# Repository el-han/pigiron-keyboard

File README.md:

# Pigiron keyboard

The Pigiron keyboard is a 80 % ISO keyboard. It may be used on it's own or together with the nmblock of the [Ingot keyboard](https://github.com/el-han/ingot-keyboard).

## Features

- QMK firmware
- Cherry MX switches
- WS2812 RGB LEDs under each switch
- PCB plate for plate mounted switches

## Todo

- Add picture
- Merge firmware into QMK project

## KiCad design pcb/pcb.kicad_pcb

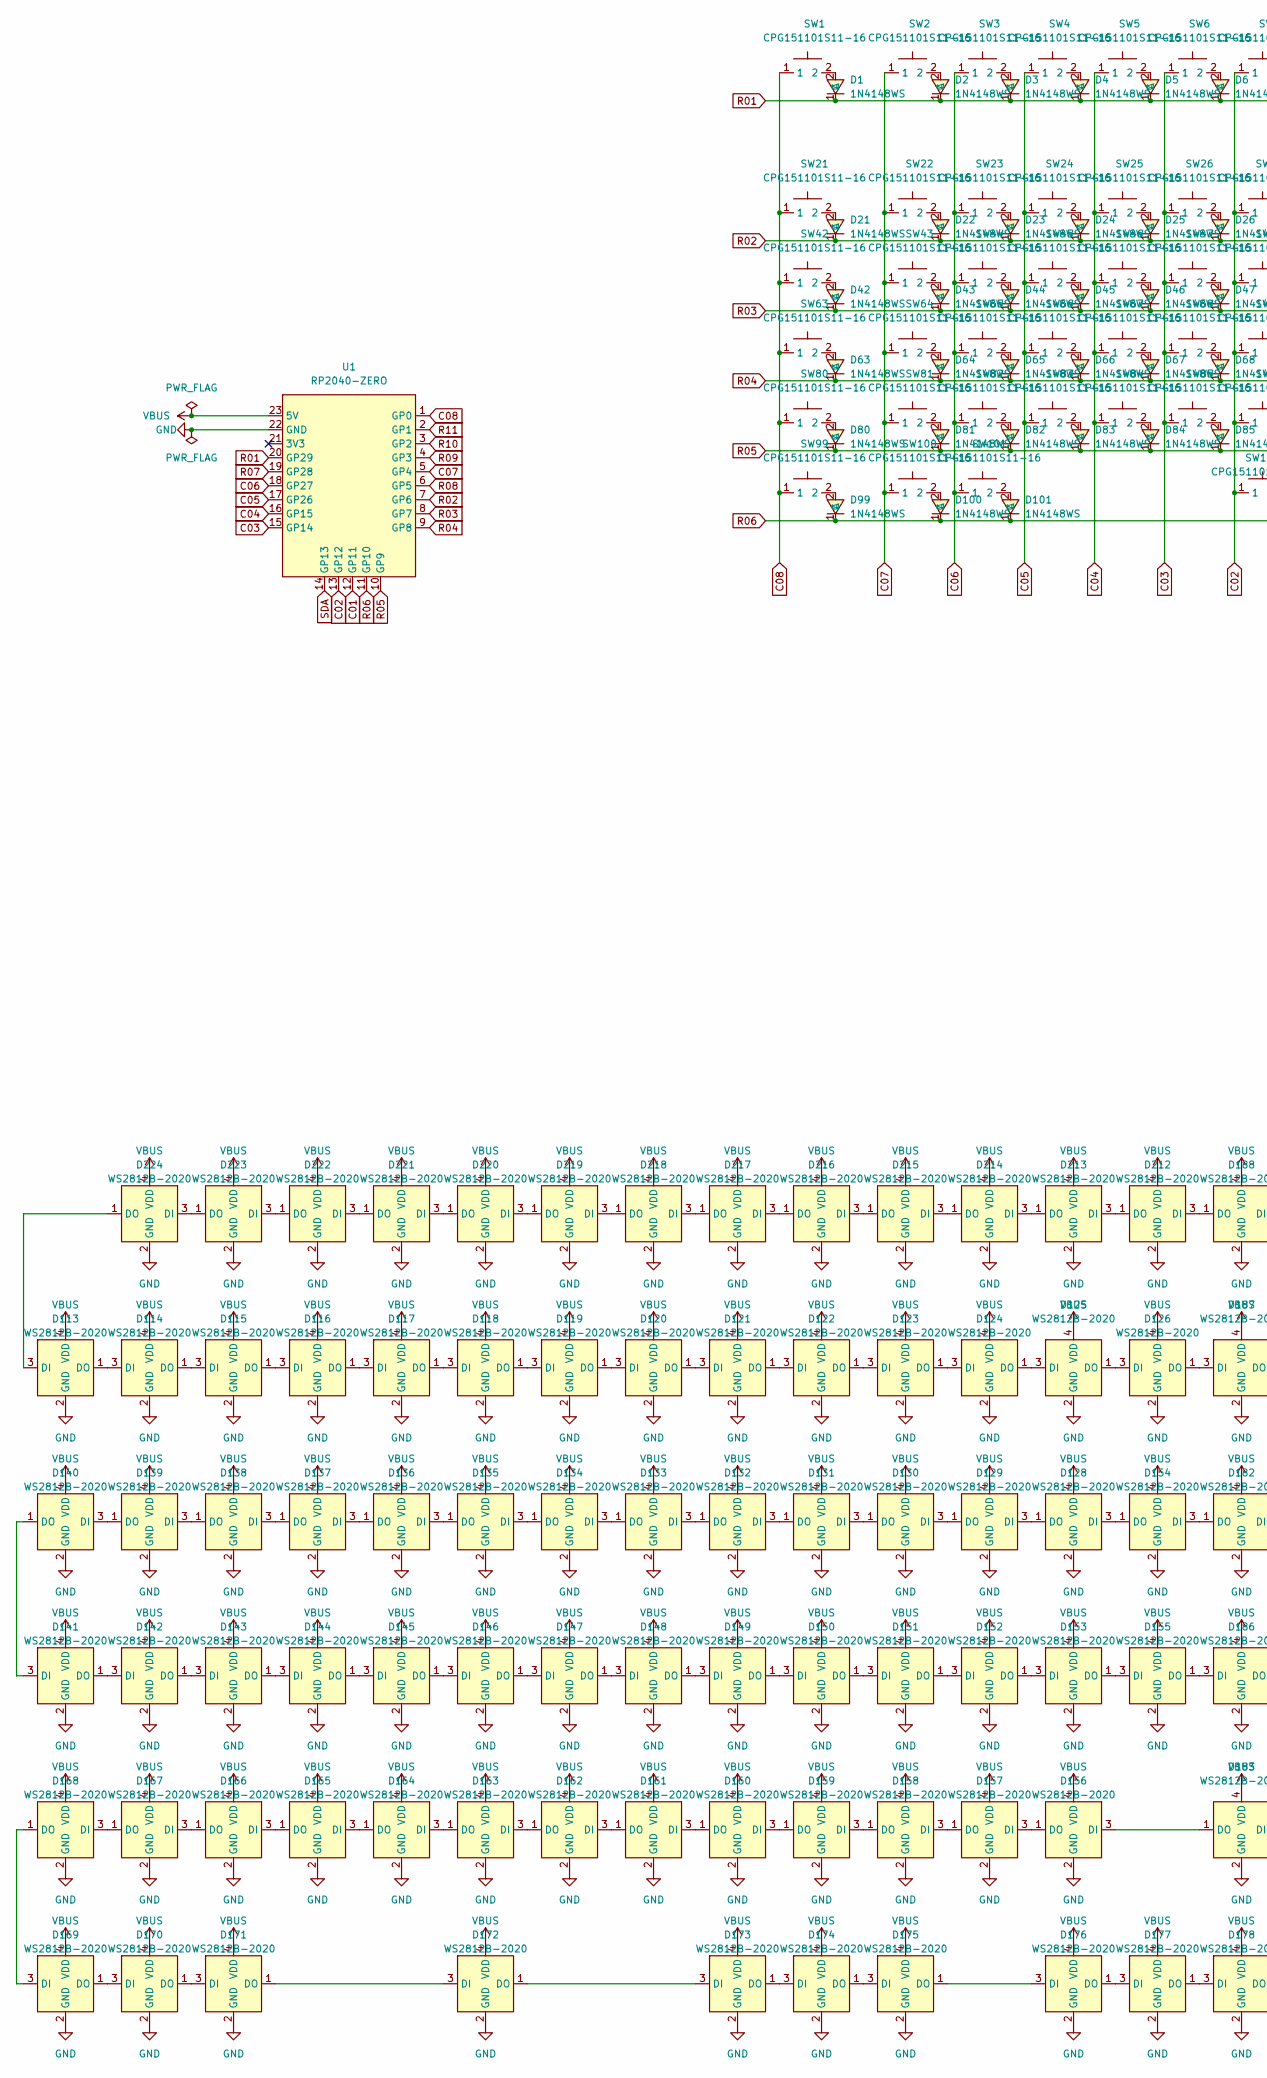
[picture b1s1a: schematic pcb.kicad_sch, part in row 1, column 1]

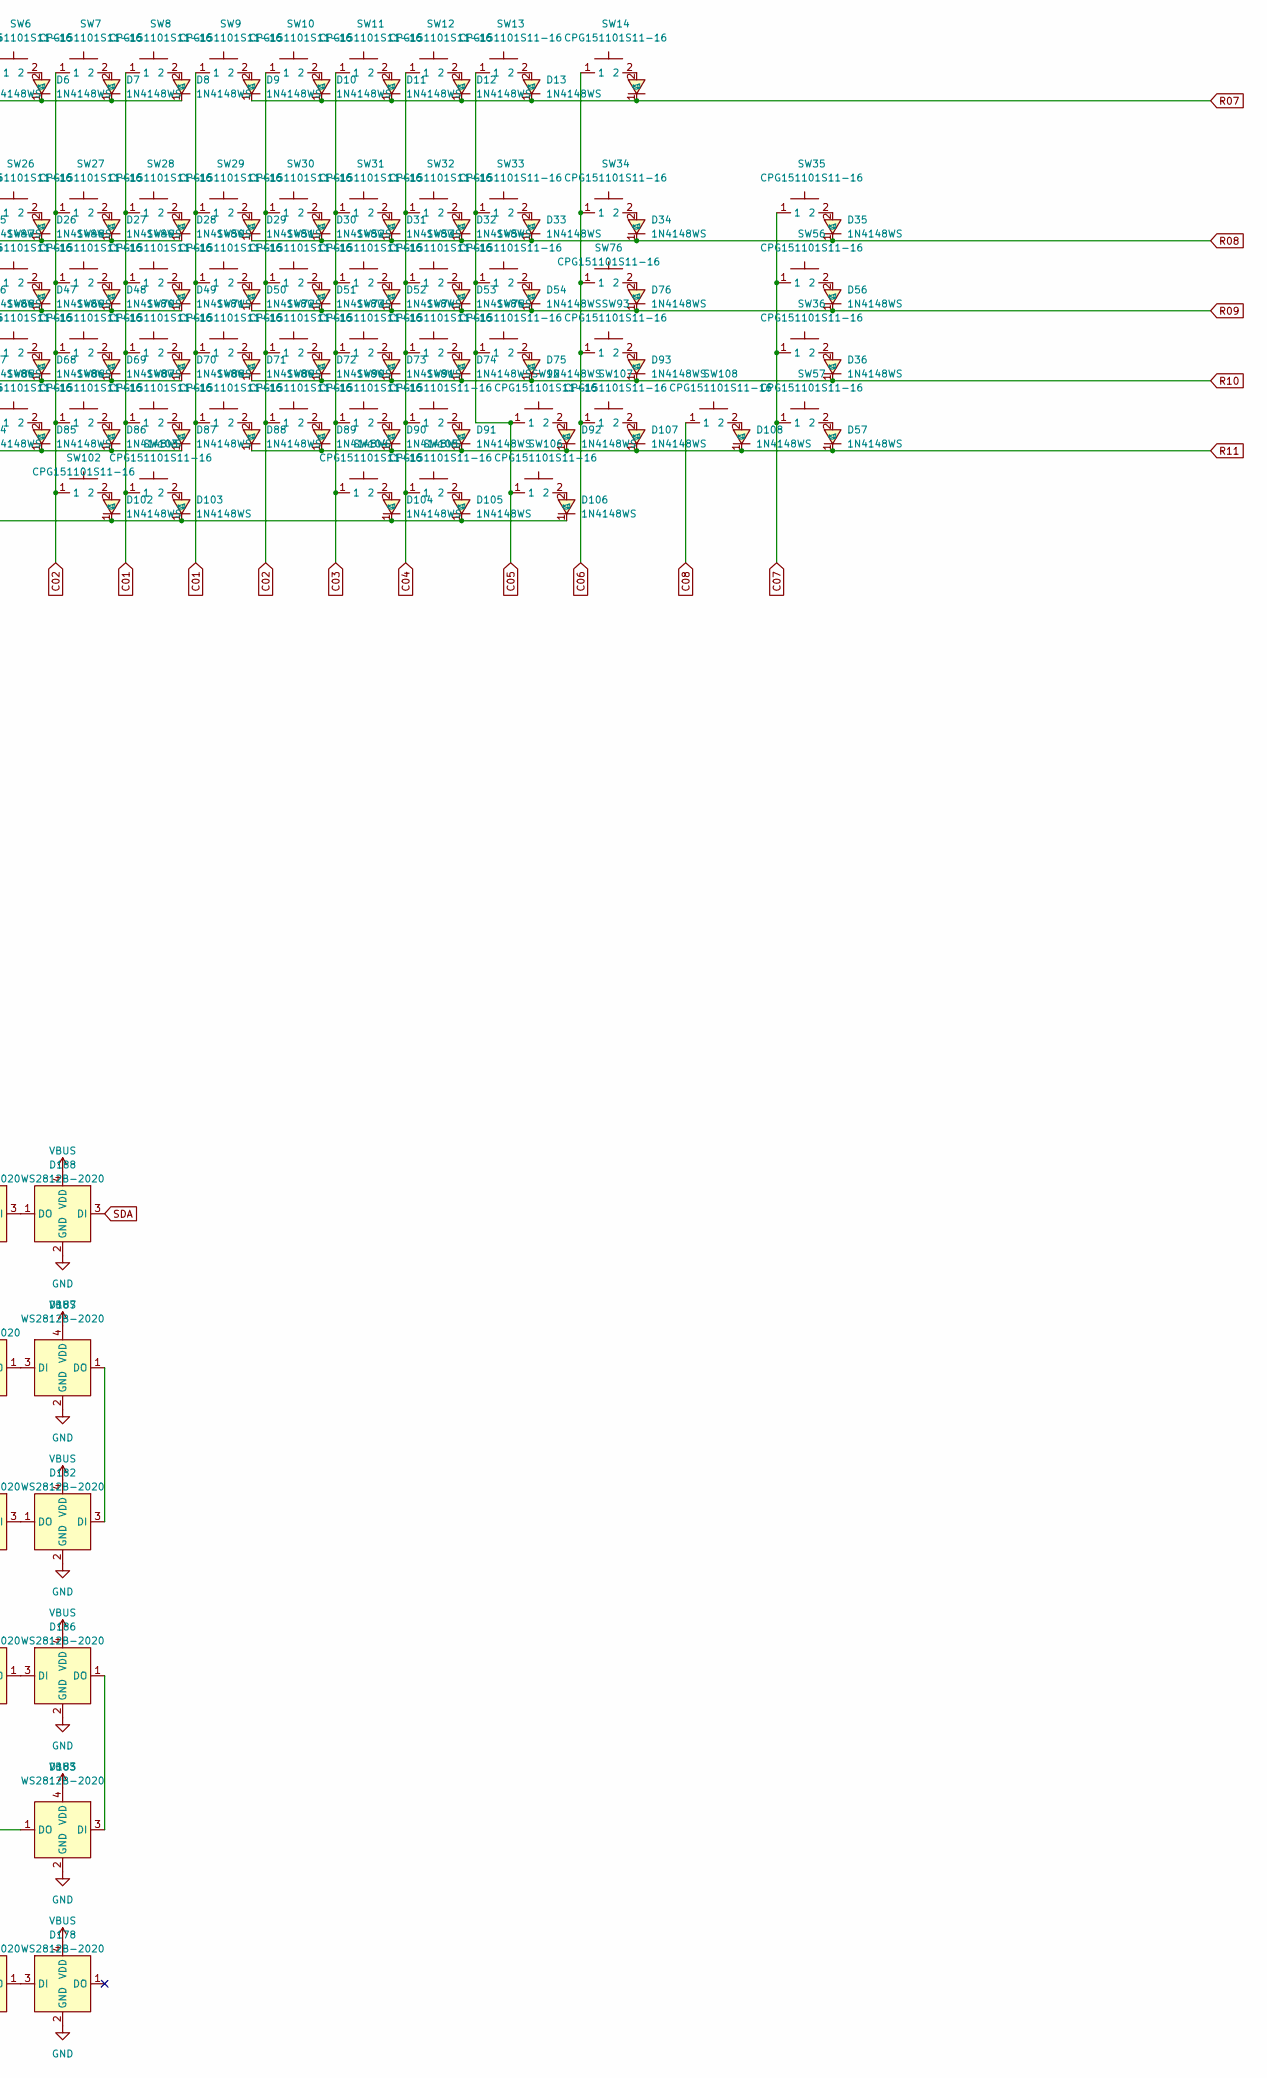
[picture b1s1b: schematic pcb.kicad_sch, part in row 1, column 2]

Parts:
D1, D2, D3, D4, D5, D6, D7, D8, D9, D10, D11, D12, D13, D14, D21, D22, D23, D24, D25, D26, D27, D28, D29, D30, D31, D32, D33, D34, D35, D36, D42, D43, D44, D45, D46, D47, D48, D49, D50, D51, D52, D53, D54, D56, D57, D63, D64, D65, D66, D67, D68, D69, D70, D71, D72, D73, D74, D75, D76, D80, D81, D82, D83, D84, D85, D86, D87, D88, D89, D90, D91, D92, D93, D99, D100, D101, D102, D103, D104, D105, D106, D107, D108: 1N4148WS; SOD-323_L1.8-W1.3-LS2.5-RD; LCSC Part C60580
D113, D114, D115, D116, D117, D118, D119, D120, D121, D122, D123, D124, D125, D126, D128, D129, D130, D131, D132, D133, D134, D135, D136, D137, D138, D139, D140, D141, D142, D143, D144, D145, D146, D147, D148, D149, D150, D151, D152, D153, D154, D155, D156, D157, D158, D159, D160, D161, D162, D163, D164, D165, D166, D167, D168, D169, D170, D171, D172, D173, D174, D175, D176, D177, D178, D182, D183, D186, D187, D188, D212, D213, D214, D215, D216, D217, D218, D219, D220, D221, D222, D223, D224: WS2812B-2020; LED-SMD_4P-L2.0-W2.0-BR-1; LCSC Part C5349955
SW1, SW2, SW3, SW4, SW5, SW6, SW7, SW8, SW9, SW10, SW11, SW12, SW13, SW14, SW21, SW22, SW23, SW24, SW25, SW26, SW27, SW28, SW29, SW30, SW31, SW32, SW33, SW35, SW36, SW43, SW44, SW45, SW46, SW47, SW48, SW49, SW50, SW51, SW52, SW53, SW54, SW56, SW57, SW64, SW65, SW66, SW67, SW68, SW69, SW70, SW71, SW72, SW73, SW74, SW75, SW81, SW82, SW83, SW84, SW85, SW86, SW87, SW88, SW89, SW90, SW91, SW93, SW100, SW104, SW106, SW107, SW108: CPG151101S11-16; SMD_KEYBOARD-SW-1.00; LCSC Part C41430893
SW34: CPG151101S11-16; SMD_KEYBOARD-SW-2.00; LCSC Part C41430893
SW42: CPG151101S11-16; SMD_KEYBOARD-SW-1.50; LCSC Part C41430893
SW63, SW92: CPG151101S11-16; SMD_KEYBOARD-SW-1.75; LCSC Part C41430893
SW76: CPG151101S11-16; SMD_KEYBOARD-SW-ENTER-ISO; LCSC Part C41430893
SW80, SW99, SW101, SW103, SW105: CPG151101S11-16; SMD_KEYBOARD-SW-1.25; LCSC Part C41430893
SW102: CPG151101S11-16; SMD_KEYBOARD-SW-6.00; LCSC Part C41430893
U1: RP2040-ZERO; COMM-SMD_RP2040-ZERO; LCSC Part C5350143

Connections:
C01: SW8.1, SW9.1, SW28.1, SW29.1, SW49.1, SW50.1, SW70.1, SW71.1, SW87.1, SW88.1, SW103.1, U1.12 (GP11)
C02: SW7.1, SW10.1, SW27.1, SW30.1, SW48.1, SW51.1, SW69.1, SW72.1, SW86.1, SW89.1, SW102.1, U1.13 (GP12)
C03: SW6.1, SW11.1, SW26.1, SW31.1, SW47.1, SW52.1, SW68.1, SW73.1, SW85.1, SW90.1, SW104.1, U1.15 (GP14)
C04: SW5.1, SW12.1, SW25.1, SW32.1, SW46.1, SW53.1, SW67.1, SW74.1, SW84.1, SW91.1, SW105.1, U1.16 (GP15)
C05: SW4.1, SW13.1, SW24.1, SW33.1, SW45.1, SW54.1, SW66.1, SW75.1, SW83.1, SW92.1, SW106.1, U1.17 (GP26)
C06: SW3.1, SW14.1, SW23.1, SW34.1, SW44.1, SW65.1, SW76.1, SW82.1, SW93.1, SW101.1, SW107.1, U1.18 (GP27)
C07: SW2.1, SW22.1, SW35.1, SW36.1, SW43.1, SW56.1, SW57.1, SW64.1, SW81.1, SW100.1, U1.5 (GP4)
C08: SW1.1, SW21.1, SW42.1, SW63.1, SW80.1, SW99.1, SW108.1, U1.1 (GP0)
GND: D113.2 (GND), D114.2 (GND), D115.2 (GND), D116.2 (GND), D117.2 (GND), D118.2 (GND), D119.2 (GND), D120.2 (GND), D121.2 (GND), D122.2 (GND), D123.2 (GND), D124.2 (GND), D125.2 (GND), D126.2 (GND), D128.2 (GND), D129.2 (GND), D130.2 (GND), D131.2 (GND), D132.2 (GND), D133.2 (GND), D134.2 (GND), D135.2 (GND), D136.2 (GND), D137.2 (GND), D138.2 (GND), D139.2 (GND), D140.2 (GND), D141.2 (GND), D142.2 (GND), D143.2 (GND), D144.2 (GND), D145.2 (GND), D146.2 (GND), D147.2 (GND), D148.2 (GND), D149.2 (GND), D150.2 (GND), D151.2 (GND), D152.2 (GND), D153.2 (GND), D154.2 (GND), D155.2 (GND), D156.2 (GND), D157.2 (GND), D158.2 (GND), D159.2 (GND), D160.2 (GND), D161.2 (GND), D162.2 (GND), D163.2 (GND), D164.2 (GND), D165.2 (GND), D166.2 (GND), D167.2 (GND), D168.2 (GND), D169.2 (GND), D170.2 (GND), D171.2 (GND), D172.2 (GND), D173.2 (GND), D174.2 (GND), D175.2 (GND), D176.2 (GND), D177.2 (GND), D178.2 (GND), D182.2 (GND), D183.2 (GND), D186.2 (GND), D187.2 (GND), D188.2 (GND), D212.2 (GND), D213.2 (GND), D214.2 (GND), D215.2 (GND), D216.2 (GND), D217.2 (GND), D218.2 (GND), D219.2 (GND), D220.2 (GND), D221.2 (GND), D222.2 (GND), D223.2 (GND), D224.2 (GND), U1.22 (GND)
unnamed: D1.2 (A), SW1.2
unnamed: D2.2 (A), SW2.2
unnamed: D3.2 (A), SW3.2
unnamed: D4.2 (A), SW4.2
unnamed: D5.2 (A), SW5.2
unnamed: D6.2 (A), SW6.2
unnamed: D7.2 (A), SW7.2
unnamed: D8.2 (A), SW8.2
unnamed: D9.2 (A), SW9.2
unnamed: D10.2 (A), SW10.2
unnamed: D11.2 (A), SW11.2
unnamed: D12.2 (A), SW12.2
unnamed: D13.2 (A), SW13.2
unnamed: D14.2 (A), SW14.2
unnamed: D21.2 (A), SW21.2
unnamed: D22.2 (A), SW22.2
unnamed: D23.2 (A), SW23.2
unnamed: D24.2 (A), SW24.2
unnamed: D25.2 (A), SW25.2
unnamed: D26.2 (A), SW26.2
unnamed: D27.2 (A), SW27.2
unnamed: D28.2 (A), SW28.2
unnamed: D29.2 (A), SW29.2
unnamed: D30.2 (A), SW30.2
unnamed: D31.2 (A), SW31.2
unnamed: D32.2 (A), SW32.2
unnamed: D33.2 (A), SW33.2
unnamed: D34.2 (A), SW34.2
unnamed: D35.2 (A), SW35.2
unnamed: D36.2 (A), SW36.2
unnamed: D42.2 (A), SW42.2
unnamed: D43.2 (A), SW43.2
unnamed: D44.2 (A), SW44.2
unnamed: D45.2 (A), SW45.2
unnamed: D46.2 (A), SW46.2
unnamed: D47.2 (A), SW47.2
unnamed: D48.2 (A), SW48.2
unnamed: D49.2 (A), SW49.2
unnamed: D50.2 (A), SW50.2
unnamed: D51.2 (A), SW51.2
unnamed: D52.2 (A), SW52.2
unnamed: D53.2 (A), SW53.2
unnamed: D54.2 (A), SW54.2
unnamed: D56.2 (A), SW56.2
unnamed: D57.2 (A), SW57.2
unnamed: D63.2 (A), SW63.2
unnamed: D64.2 (A), SW64.2
unnamed: D65.2 (A), SW65.2
unnamed: D66.2 (A), SW66.2
unnamed: D67.2 (A), SW67.2
unnamed: D68.2 (A), SW68.2
unnamed: D69.2 (A), SW69.2
unnamed: D70.2 (A), SW70.2
unnamed: D71.2 (A), SW71.2
unnamed: D72.2 (A), SW72.2
unnamed: D73.2 (A), SW73.2
unnamed: D74.2 (A), SW74.2
unnamed: D75.2 (A), SW75.2
unnamed: D76.2 (A), SW76.2
unnamed: D80.2 (A), SW80.2
unnamed: D81.2 (A), SW81.2
unnamed: D82.2 (A), SW82.2
unnamed: D83.2 (A), SW83.2
unnamed: D84.2 (A), SW84.2
unnamed: D85.2 (A), SW85.2
unnamed: D86.2 (A), SW86.2
unnamed: D87.2 (A), SW87.2
unnamed: D88.2 (A), SW88.2
unnamed: D89.2 (A), SW89.2
unnamed: D90.2 (A), SW90.2
unnamed: D91.2 (A), SW91.2
unnamed: D92.2 (A), SW92.2
unnamed: D93.2 (A), SW93.2
unnamed: D99.2 (A), SW99.2
unnamed: D100.2 (A), SW100.2
unnamed: D101.2 (A), SW101.2
unnamed: D102.2 (A), SW102.2
unnamed: D103.2 (A), SW103.2
unnamed: D104.2 (A), SW104.2
unnamed: D105.2 (A), SW105.2
unnamed: D106.2 (A), SW106.2
unnamed: D107.2 (A), SW107.2
unnamed: D108.2 (A), SW108.2
unnamed: D113.3 (DI), D224.1 (DO)
unnamed: D113.1 (DO), D114.3 (DI)
unnamed: D114.1 (DO), D115.3 (DI)
unnamed: D115.1 (DO), D116.3 (DI)
unnamed: D116.1 (DO), D117.3 (DI)
unnamed: D117.1 (DO), D118.3 (DI)
unnamed: D118.1 (DO), D119.3 (DI)
unnamed: D119.1 (DO), D120.3 (DI)
unnamed: D120.1 (DO), D121.3 (DI)
unnamed: D121.1 (DO), D122.3 (DI)
unnamed: D122.1 (DO), D123.3 (DI)
unnamed: D123.1 (DO), D124.3 (DI)
unnamed: D124.1 (DO), D125.3 (DI)
unnamed: D125.1 (DO), D126.3 (DI)
unnamed: D126.1 (DO), D187.3 (DI)
unnamed: D128.3 (DI), D154.1 (DO)
unnamed: D128.1 (DO), D129.3 (DI)
unnamed: D129.1 (DO), D130.3 (DI)
unnamed: D130.1 (DO), D131.3 (DI)
unnamed: D131.1 (DO), D132.3 (DI)
unnamed: D132.1 (DO), D133.3 (DI)
unnamed: D133.1 (DO), D134.3 (DI)
unnamed: D134.1 (DO), D135.3 (DI)
unnamed: D135.1 (DO), D136.3 (DI)
unnamed: D136.1 (DO), D137.3 (DI)
unnamed: D137.1 (DO), D138.3 (DI)
unnamed: D138.1 (DO), D139.3 (DI)
unnamed: D139.1 (DO), D140.3 (DI)
unnamed: D140.1 (DO), D141.3 (DI)
unnamed: D141.1 (DO), D142.3 (DI)
unnamed: D142.1 (DO), D143.3 (DI)
unnamed: D143.1 (DO), D144.3 (DI)
unnamed: D144.1 (DO), D145.3 (DI)
unnamed: D145.1 (DO), D146.3 (DI)
unnamed: D146.1 (DO), D147.3 (DI)
unnamed: D147.1 (DO), D148.3 (DI)
unnamed: D148.1 (DO), D149.3 (DI)
unnamed: D149.1 (DO), D150.3 (DI)
unnamed: D150.1 (DO), D151.3 (DI)
unnamed: D151.1 (DO), D152.3 (DI)
unnamed: D152.1 (DO), D153.3 (DI)
unnamed: D153.1 (DO), D155.3 (DI)
unnamed: D154.3 (DI), D182.1 (DO)
unnamed: D155.1 (DO), D186.3 (DI)
unnamed: D156.3 (DI), D183.1 (DO)
unnamed: D156.1 (DO), D157.3 (DI)
unnamed: D157.1 (DO), D158.3 (DI)
unnamed: D158.1 (DO), D159.3 (DI)
unnamed: D159.1 (DO), D160.3 (DI)
unnamed: D160.1 (DO), D161.3 (DI)
unnamed: D161.1 (DO), D162.3 (DI)
unnamed: D162.1 (DO), D163.3 (DI)
unnamed: D163.1 (DO), D164.3 (DI)
unnamed: D164.1 (DO), D165.3 (DI)
unnamed: D165.1 (DO), D166.3 (DI)
unnamed: D166.1 (DO), D167.3 (DI)
unnamed: D167.1 (DO), D168.3 (DI)
unnamed: D168.1 (DO), D169.3 (DI)
unnamed: D169.1 (DO), D170.3 (DI)
unnamed: D170.1 (DO), D171.3 (DI)
unnamed: D171.1 (DO), D172.3 (DI)
unnamed: D172.1 (DO), D173.3 (DI)
unnamed: D173.1 (DO), D174.3 (DI)
unnamed: D174.1 (DO), D175.3 (DI)
unnamed: D175.1 (DO), D176.3 (DI)
unnamed: D176.1 (DO), D177.3 (DI)
unnamed: D177.1 (DO), D178.3 (DI)
unnamed: D182.3 (DI), D187.1 (DO)
unnamed: D183.3 (DI), D186.1 (DO)
unnamed: D188.1 (DO), D212.3 (DI)
unnamed: D212.1 (DO), D213.3 (DI)
unnamed: D213.1 (DO), D214.3 (DI)
unnamed: D214.1 (DO), D215.3 (DI)
unnamed: D215.1 (DO), D216.3 (DI)
unnamed: D216.1 (DO), D217.3 (DI)
unnamed: D217.1 (DO), D218.3 (DI)
unnamed: D218.1 (DO), D219.3 (DI)
unnamed: D219.1 (DO), D220.3 (DI)
unnamed: D220.1 (DO), D221.3 (DI)
unnamed: D221.1 (DO), D222.3 (DI)
unnamed: D222.1 (DO), D223.3 (DI)
unnamed: D223.1 (DO), D224.3 (DI)
R01: D1.1 (C), D2.1 (C), D3.1 (C), D4.1 (C), D5.1 (C), D6.1 (C), D7.1 (C), D8.1 (C), U1.20 (GP29)
R02: D21.1 (C), D22.1 (C), D23.1 (C), D24.1 (C), D25.1 (C), D26.1 (C), D27.1 (C), D28.1 (C), U1.7 (GP6)
R03: D42.1 (C), D43.1 (C), D44.1 (C), D45.1 (C), D46.1 (C), D47.1 (C), D48.1 (C), D49.1 (C), U1.8 (GP7)
R04: D63.1 (C), D64.1 (C), D65.1 (C), D66.1 (C), D67.1 (C), D68.1 (C), D69.1 (C), D70.1 (C), U1.9 (GP8)
R05: D80.1 (C), D81.1 (C), D82.1 (C), D83.1 (C), D84.1 (C), D85.1 (C), D86.1 (C), D87.1 (C), U1.10 (GP9)
R06: D99.1 (C), D100.1 (C), D101.1 (C), D102.1 (C), D103.1 (C), D104.1 (C), D105.1 (C), D106.1 (C), U1.11 (GP10)
R07: D9.1 (C), D10.1 (C), D11.1 (C), D12.1 (C), D13.1 (C), D14.1 (C), U1.19 (GP28)
R08: D29.1 (C), D30.1 (C), D31.1 (C), D32.1 (C), D33.1 (C), D34.1 (C), D35.1 (C), U1.6 (GP5)
R09: D50.1 (C), D51.1 (C), D52.1 (C), D53.1 (C), D54.1 (C), D56.1 (C), D76.1 (C), U1.4 (GP3)
R10: D36.1 (C), D71.1 (C), D72.1 (C), D73.1 (C), D74.1 (C), D75.1 (C), D93.1 (C), U1.3 (GP2)
R11: D57.1 (C), D88.1 (C), D89.1 (C), D90.1 (C), D91.1 (C), D92.1 (C), D107.1 (C), D108.1 (C), U1.2 (GP1)
SDA: D188.3 (DI), U1.14 (GP13)
VBUS: D113.4 (VDD), D114.4 (VDD), D115.4 (VDD), D116.4 (VDD), D117.4 (VDD), D118.4 (VDD), D119.4 (VDD), D120.4 (VDD), D121.4 (VDD), D122.4 (VDD), D123.4 (VDD), D124.4 (VDD), D125.4 (VDD), D126.4 (VDD), D128.4 (VDD), D129.4 (VDD), D130.4 (VDD), D131.4 (VDD), D132.4 (VDD), D133.4 (VDD), D134.4 (VDD), D135.4 (VDD), D136.4 (VDD), D137.4 (VDD), D138.4 (VDD), D139.4 (VDD), D140.4 (VDD), D141.4 (VDD), D142.4 (VDD), D143.4 (VDD), D144.4 (VDD), D145.4 (VDD), D146.4 (VDD), D147.4 (VDD), D148.4 (VDD), D149.4 (VDD), D150.4 (VDD), D151.4 (VDD), D152.4 (VDD), D153.4 (VDD), D154.4 (VDD), D155.4 (VDD), D156.4 (VDD), D157.4 (VDD), D158.4 (VDD), D159.4 (VDD), D160.4 (VDD), D161.4 (VDD), D162.4 (VDD), D163.4 (VDD), D164.4 (VDD), D165.4 (VDD), D166.4 (VDD), D167.4 (VDD), D168.4 (VDD), D169.4 (VDD), D170.4 (VDD), D171.4 (VDD), D172.4 (VDD), D173.4 (VDD), D174.4 (VDD), D175.4 (VDD), D176.4 (VDD), D177.4 (VDD), D178.4 (VDD), D182.4 (VDD), D183.4 (VDD), D186.4 (VDD), D187.4 (VDD), D188.4 (VDD), D212.4 (VDD), D213.4 (VDD), D214.4 (VDD), D215.4 (VDD), D216.4 (VDD), D217.4 (VDD), D218.4 (VDD), D219.4 (VDD), D220.4 (VDD), D221.4 (VDD), D222.4 (VDD), D223.4 (VDD), D224.4 (VDD), U1.23 (5V)

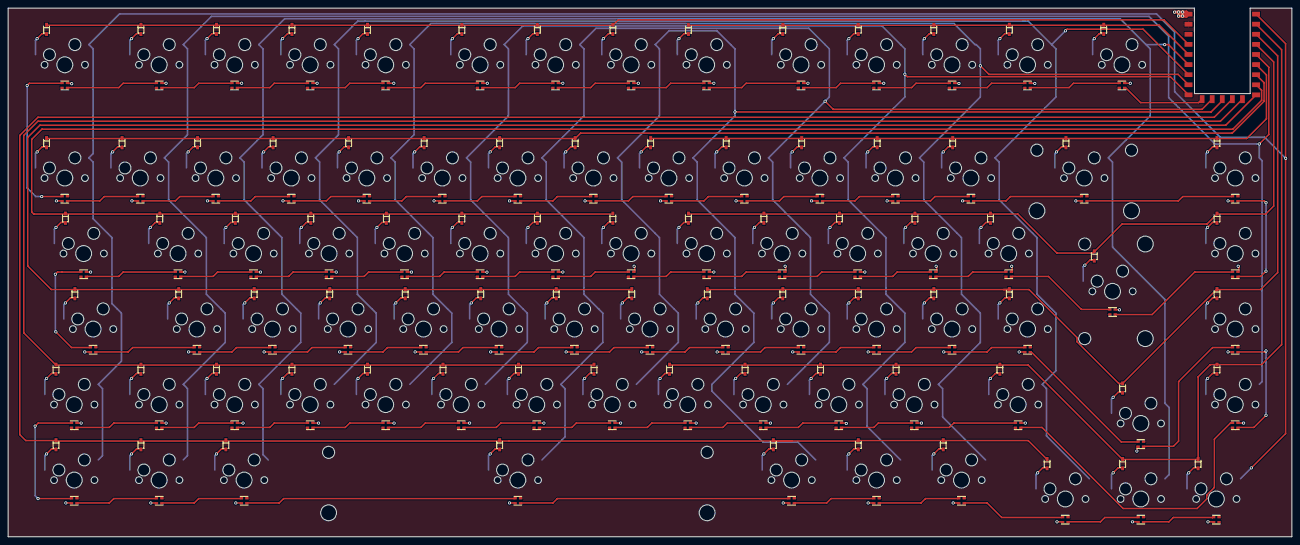
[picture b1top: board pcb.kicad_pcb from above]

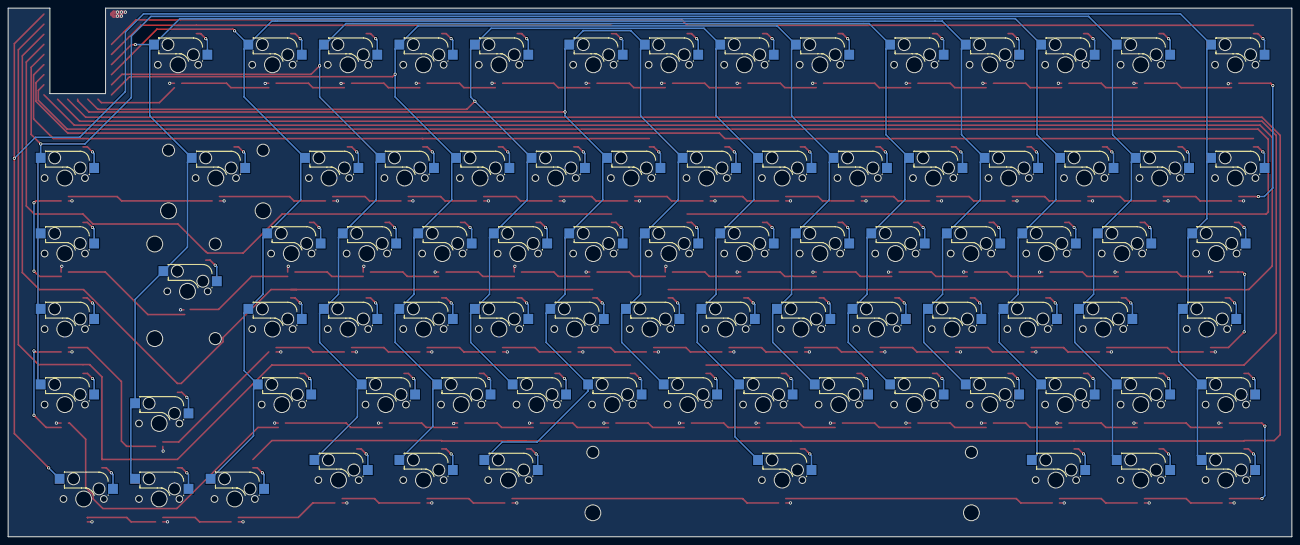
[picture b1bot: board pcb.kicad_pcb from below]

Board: 2 copper layers, 323.0 x 133.0 mm, 250 parts (83 on the bottom side), 187 nets.

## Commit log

2021-07-20 update schematics
2021-07-20 add plate
2021-07-20 add keyboard layout
2024-10-25 add readme
2024-11-08 add staggered ISO layout
2024-11-17 design finished
2024-11-17 drc clean
2024-11-17 clean up
